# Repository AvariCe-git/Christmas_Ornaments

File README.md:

Simple christmas ornament with attiny13a.
What I'm trying to do is have an LED to flash for approximately 20 days with a single CR 2032 battery.
Theoretically this is possible if the circuit draws ~400 μA of current on average, which on a breadboard it does. 
I will add the pcb designs when I have something that works.

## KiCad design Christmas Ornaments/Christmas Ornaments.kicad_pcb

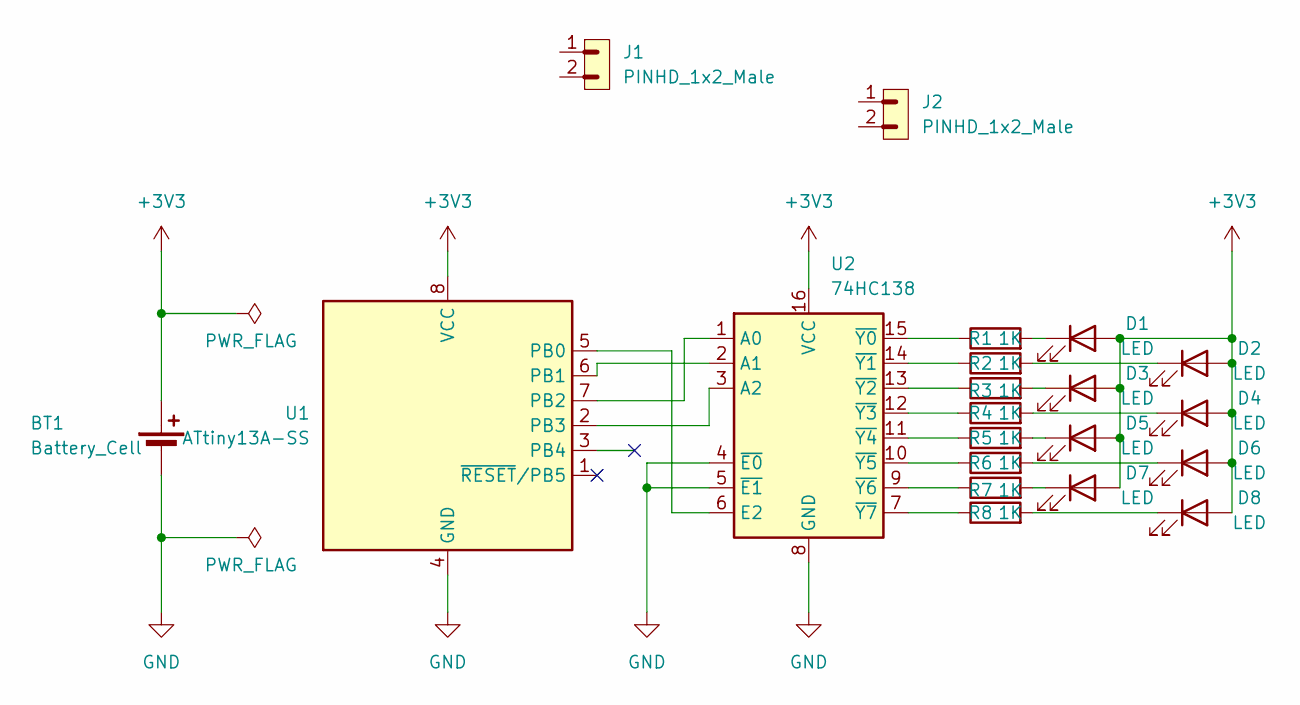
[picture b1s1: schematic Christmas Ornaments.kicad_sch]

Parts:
BT1: Battery_Cell; BatteryHolder_MYOUNG_BS-07-A1BJ001_CR2032
D1, D2, D3, D4, D5, D6, D7, D8: LED; LED_0805_2012Metric
J1, J2: PINHD_1x2_Male; PinHeader_1x02_P2.54mm_Vertical
R1, R2, R3, R4, R5, R6, R7, R8: 1K; R_0805_2012Metric
U1: ATtiny13A-SS; SOIC-8_3.9x4.9mm_P1.27mm
U2: 74HC138; SOIC-16_3.9x9.9mm_P1.27mm

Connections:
+3V3: BT1.1 (+), D1.2 (A), D2.2 (A), D3.2 (A), D4.2 (A), D5.2 (A), D6.2 (A), D7.2 (A), D8.2 (A), U1.8 (VCC), U2.16 (VCC)
GND: BT1.2 (-), U1.4 (GND), U2.4 (~E0), U2.5 (~E1), U2.8 (GND)
unnamed: D1.1 (K), R1.2
unnamed: D2.1 (K), R2.2
unnamed: D3.1 (K), R3.2
unnamed: D4.1 (K), R4.2
unnamed: D5.1 (K), R5.2
unnamed: D6.1 (K), R6.2
unnamed: D7.1 (K), R7.2
unnamed: D8.1 (K), R8.2
unnamed: U1.5 (PB0), U2.6 (E2)
unnamed: U1.6 (PB1), U2.2 (A1)
unnamed: U1.7 (PB2), U2.1 (A0)
unnamed: U1.2 (PB3), U2.3 (A2)
unnamed: R1.1, U2.15 (~Y0)
unnamed: R2.1, U2.14 (~Y1)
unnamed: R3.1, U2.13 (~Y2)
unnamed: R4.1, U2.12 (~Y3)
unnamed: R5.1, U2.11 (~Y4)
unnamed: R6.1, U2.10 (~Y5)
unnamed: R7.1, U2.9 (~Y6)
unnamed: R8.1, U2.7 (~Y7)

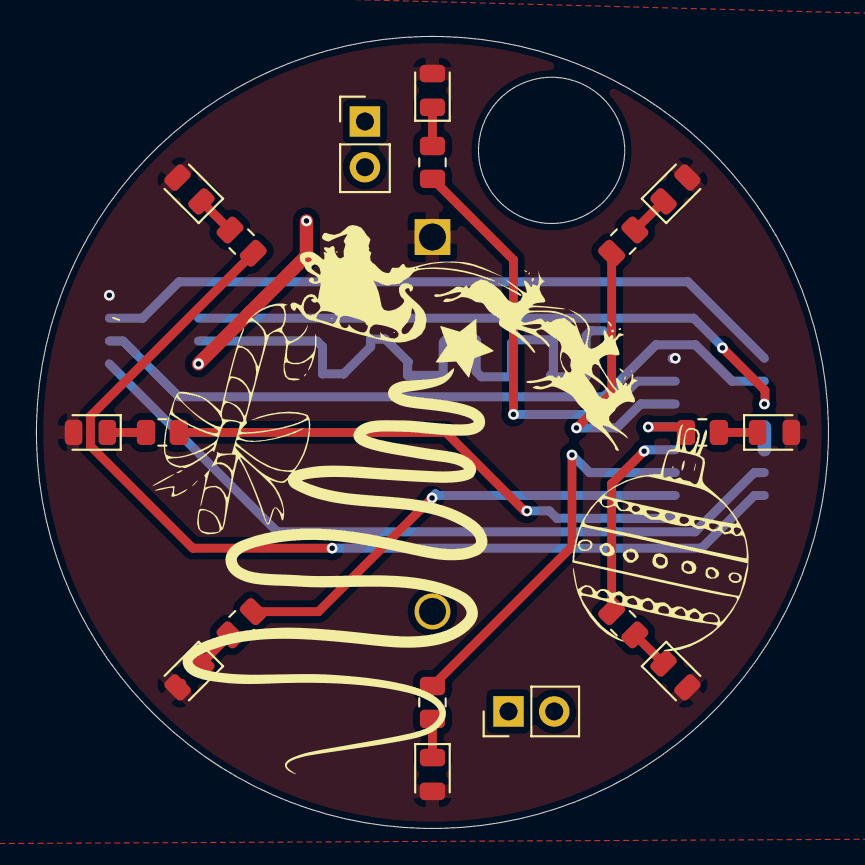
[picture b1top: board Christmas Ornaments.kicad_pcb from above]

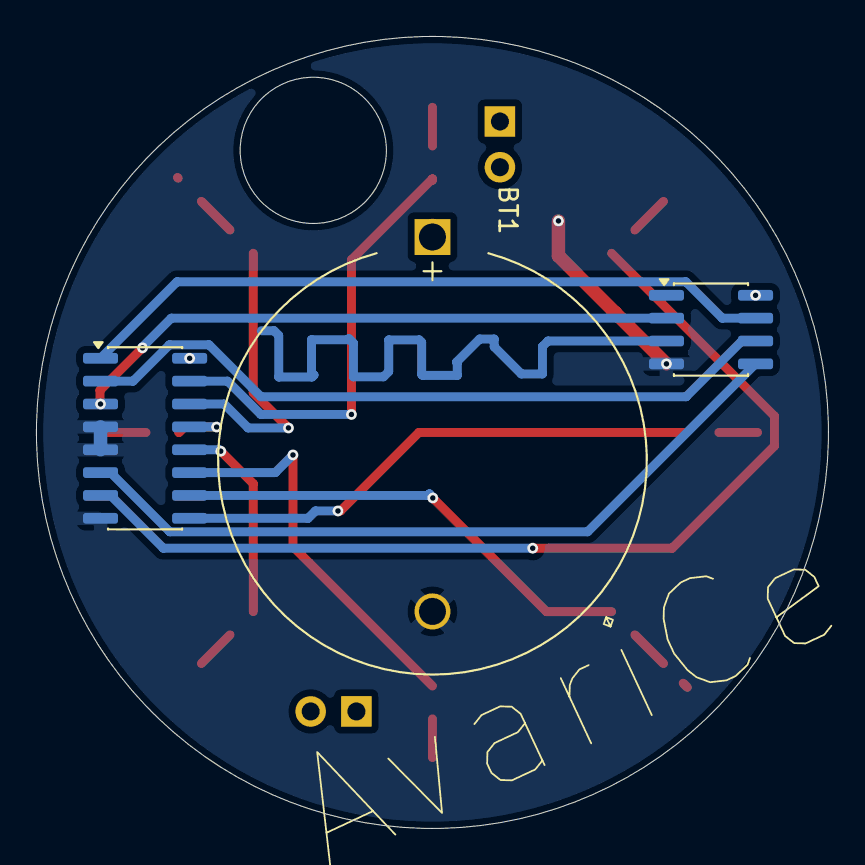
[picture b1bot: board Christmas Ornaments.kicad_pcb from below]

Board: 2 copper layers, 44.0 x 44.0 mm, 21 parts (3 on the bottom side), 22 nets.

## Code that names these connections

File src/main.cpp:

#include <Arduino.h>

long random_int(long x);

const int pin_enable = PB0;
const int pinA = PB1;
const int pinB = PB2;
const int pinC = PB3;
const int random_read = PB4;

const unsigned int delay_timer = 250;
const int i_max = 128;
long random_number = 0;

unsigned int leds[8][3] =   {{0,0,0}
                            ,{0,0,1}
                            ,{0,1,0}
                            ,{0,1,1}
                            ,{1,0,0}
                            ,{1,0,1}
                            ,{1,1,0}
                            ,{1,1,1}
                            };

void setup(){

    DIDR0 = 0x3F; // disable digital input buffers
    ACSR |= (1 << ACD); // disable analog comparator
    wdt_disable(); // disable watchdog timer

    //Black magic for the pwm to work. I don't understand it, but it works
    TCCR0A  = ((5<<WGM00) |(2<<COM0A0)) ; // mode Phase correct PWM
    TCCR0B  = ( (1<<CS00)); // clock input don't divide
    OCR0A = 0; // now it seems to be duty cycle - initial value

    pinMode(pin_enable,OUTPUT);
    pinMode(pinA,OUTPUT);
    pinMode(pinB,OUTPUT);
    pinMode(pinC,OUTPUT);
    pinMode(random_read,INPUT);
    
    randomSeed((random_read));
    random_number = random_int(0); 
}

void loop(){

    int i = 0;
    
    digitalWrite(pinA,leds[random_number][0]);
    digitalWrite(pinB,leds[random_number][1]);
    digitalWrite(pinC,leds[random_number][2]);
    
    digitalWrite(pin_enable, 1);
    
    for (i = 0; i < i_max; i++){
        OCR0A = i;
        delayMicroseconds(delay_timer);
    }
    
    for (i = i_max; i > 0; i--){
        OCR0A = i;
        delayMicroseconds(delay_timer);
    }
    
    digitalWrite(pin_enable, 0);
    
    random_number = random_int(random_number);
}

long random_int(long x){
    
    long y = random(0,8);
    
    if (y == x){
        y = random_int(y);
    }

    return y;
}

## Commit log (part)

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2026-03-28 Initial Release
2026-03-28 Added schematic
2026-03-28 Removed backups
